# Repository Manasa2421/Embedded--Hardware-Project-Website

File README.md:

# Embedded--Hardware-Project-Website

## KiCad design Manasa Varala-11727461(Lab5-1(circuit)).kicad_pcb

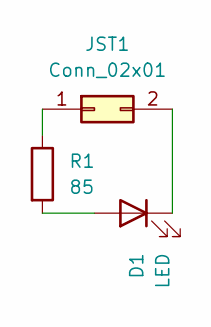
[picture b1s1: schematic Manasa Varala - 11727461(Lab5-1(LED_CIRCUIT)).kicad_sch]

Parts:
D1: LED; LED_D3.0mm
JST1: Conn_02x01; JST_PH_S2B-PH-K_1x02_P2.00mm_Horizontal
R1: 85; R_Axial_DIN0207_L6.3mm_D2.5mm_P2.54mm_Vertical

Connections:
unnamed: D1.2 (A), R1.2
unnamed: D1.1 (K), JST1.2
unnamed: JST1.1, R1.1

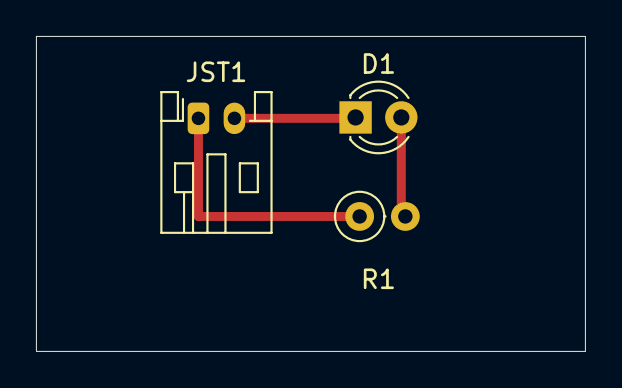
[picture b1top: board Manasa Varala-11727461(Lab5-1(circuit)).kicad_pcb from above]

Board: 2 copper layers, 30.5 x 17.5 mm, 3 parts (0 on the bottom side), 3 nets.

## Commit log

2025-01-15 Rename pexels-frank-cone-140140-3250638.jpg to path-to-your-image.jpg
